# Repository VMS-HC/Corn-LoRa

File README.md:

A not so basic electronic project... This is a LoRa Board which is great for meshtastic but not great for my sanity when routing! This has a SX1262 radio chip and uses a RP2040 for the microcontroller along with a crystal oscillator for the RP2040 like any normal dev board. Corn LoRa also includes a *0900FM15D0039* as a IPD (integrated passive device) by Johanson which controls the balun and filtering (868-915MHz, may be different footprint) To switch between TX and RX, it uses an RF switch, controlled by DIO2; along with a PE4259 for a 2 channel switcher (as mentioned above!). It also uses a bulky non-standard Conn for an antenna! 
Ty for looking and have a good day! <3!
# Corn-LoRa PCB photo!
 3D Render photo!
 Schematic!

## FAQ

#### CAD? 
 Here! https://cad.onshape.com/documents/798bf0a7dc11aab5a7bf582d/w/40104e5f41c3cdcce0e1b7a0/e/90af93f35366755db2896de5?renderMode=0&uiState=6ae0c972e6e866bde4647e71
 
#### BOM?

There are 2 BOM technically one has the LCSC part numbers and the others is a quote from LCSC with links to parts too!

#### Is this good for beginners?

Yes and no, if you know EDA/Kicad basics and could make a dev board without trouble you should be able to make this!

#### How many layers is the PCB?

This is a 4 layer PCB with a Earth layer and a +3V3 layer!

#### Can I contribute?

YES YOU CAN!!!! Take a peek at the Contributing section for a better guide on contributing!

## Authors

- [@bobert3d](https://www.github.com/Bobert3D)

- [@vms-hc](https://www.github.com/VMS-HC)

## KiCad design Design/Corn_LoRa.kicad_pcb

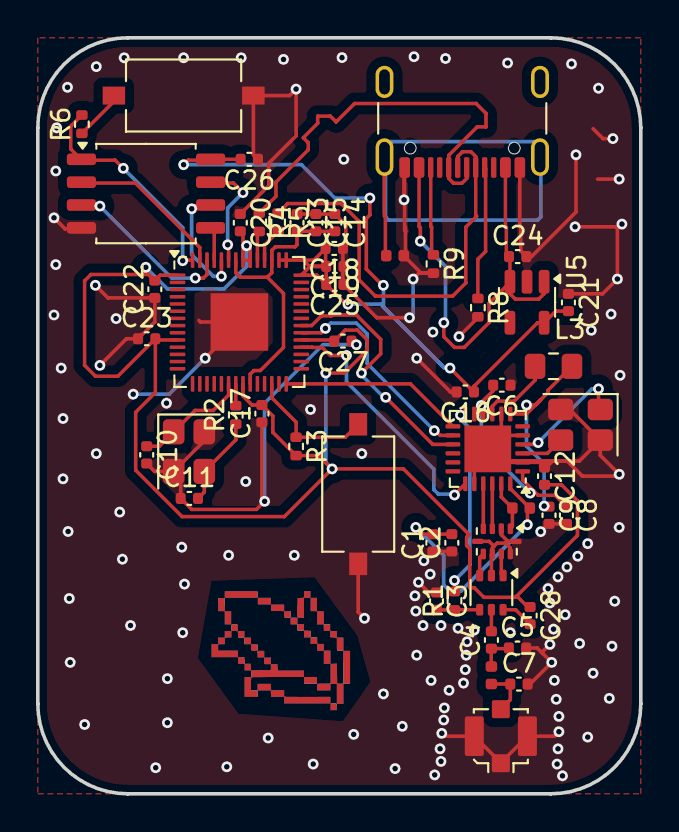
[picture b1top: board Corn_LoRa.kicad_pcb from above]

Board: 4 copper layers, 33.5 x 42.0 mm, 52 parts (0 on the bottom side), 43 nets.

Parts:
C1, C2: 47nF; C_0402_1005Metric
C3: 1nF; C_0402_1005Metric
C4: 39pF; C_0402_1005Metric
C5, C7, C12: 3.3pF; C_0402_1005Metric
C6, C8, C13, C14, C17, C18, C19, C20, C21, C22, C23, C26, C27: 100nF; C_0402_1005Metric
C9: 470nF; C_0402_1005Metric
C10, C11: 15pF; C_0402_1005Metric
C15, C16: 1uF; C_0402_1005Metric
C24, C25: 10uF; C_0402_1005Metric
C28: 10nF; C_0402_1005Metric
FB1: BLM15AX102SN1D; L_0402_1005Metric
FL1: 0900FM15K0039; Balun_Johanson_0900FM15K0039
J1: USB_C_Receptacle_USB2.0_16P; USB_C_Receptacle_GCT_USB4105-xx-A_16P_TopMnt_Horizontal
J2: Conn_Coaxial_Small; U.FL_Molex_MCRF_73412-0110_Vertical
L1, L2: 9.1nH; L_0402_1005Metric
L3: 15uH; L_0805_2012Metric_Pad1.15x1.40mm_HandSolder
R1: 100; R_0402_1005Metric
R2, R6: 1K; R_0402_1005Metric
R3: 10K; R_0402_1005Metric
R4, R5: 27.4; R_0402_1005Metric
R8, R9: 5.1K; R_0402_1005Metric
SW1: BOOTSEL; SW_Tactile_SPST_NO_Straight_CK_PTS636Sx25SMTRLFS
SW2: RESET; SW_Tactile_SPST_NO_Straight_CK_PTS636Sx25SMTRLFS
U1: PE4259; SOT-363_SC-70-6
U2: SX1262IMLTRT; QFN-24-1EP_4x4mm_P0.5mm_EP2.6x2.6mm
U3: W25Q128JVS; SOIC-8_5.3x5.3mm_P1.27mm
U4: RP2040; QFN-56-1EP_7x7mm_P0.4mm_EP3.2x3.2mm
U5: AP2112K-3.3; SOT-23-5
Y1: 32MHz; Crystal_SMD_3225-4Pin_3.2x2.5mm
Y2: 12MHz; Crystal_SMD_Abracon_ABM8G-4Pin_3.2x2.5mm

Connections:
+1V1: C13.2, C14.2, C15.2, U4.23 (DVDD), U4.45 (VREG_VOUT), U4.50 (DVDD)
+3V3: C12.2, C16.1, C17.2, C18.2, C19.2, C20.2, C21.2, C22.2, C23.2, C25.2, C26.2, C27.2, C28.1, R3.2, U3.8 (VCC), U4.1 (IOVDD), U4.10 (IOVDD), U4.22 (IOVDD), U4.33 (IOVDD), U4.42 (IOVDD), U4.43 (ADC_AVDD), U4.44 (VREG_IN), U4.48 (USB_VDD), U4.49 (IOVDD), U5.5 (VOUT)
/QSPI_SCLK: U3.6 (CLK), U4.52 (QSPI_SCLK)
/QSPI_SD0: U3.5 (DI/IO_{0}), U4.53 (QSPI_SD0)
/QSPI_SD1: U3.2 (DO/IO_{1}), U4.55 (QSPI_SD1)
/QSPI_SD2: U3.3 (~WP/IO_{2}), U4.54 (QSPI_SD2)
/QSPI_SD3: U3.7 (~HOLD/~RESET/IO_{3}), U4.51 (QSPI_SD3)
/QSPI_SS: R6.2, U3.1 (~CS), U4.56 (QSPI_SS)
/RUN: R3.1, SW2.2, U4.26 (RUN)
/SX_BUSY: U2.14 (BUSY), U4.34 (GPIO22)
/SX_DIO1: U2.13 (DIO1), U4.28 (GPIO17)
/SX_DIO2: R1.2, U2.12 (DIO2)
/SX_NRST: U2.15 (~RESET), U4.35 (GPIO23)
/SX_NSS: U2.19 (NSS), U4.32 (GPIO21)
/SX_RFI_N: FL1.3 (RFI_N), U2.22 (RFI_N)
/SX_RFI_P: FL1.4 (RFI_P), U2.21 (RFI_P)
/SX_RFO: FL1.1 (RFO), L1.2, U2.23 (RFO)
/SX_VR_PA: C1.2, C2.2, L1.1, U2.24 (VR_PA)
/SX_XTA: U2.3 (XTA), Y1.3
/SX_XTB: U2.4 (XTB), Y1.1
/USB_DM: J1.A7 (D-), J1.B7 (D-), R5.1
/USB_DP: J1.A6 (D+), J1.B6 (D+), R4.1
/XIN: C10.1, U4.20 (XIN), Y2.1
/XOUT: R2.2, U4.21 (XOUT)
Earth: C1.1, C2.1, C3.1, C5.2, C6.1, C7.2, C8.2, C9.2, C10.2, C11.1, C12.1, C13.1, C14.1, C15.1, C16.2, C17.1, C18.1, C19.1, C20.1, C21.1, C22.1, C23.1, C24.2, C25.1, C26.1, C27.1, FB1.2, FL1.2 (GND), FL1.5 (GND), FL1.7 (GND), FL1.9 (GND), FL1.10 (GND), J1.A1 (GND), J1.A12 (GND), J1.B1 (GND), J1.B12 (GND), J2.2 (Ext), R8.2, R9.2, SW1.1, SW2.1, U1.2 (GND), U2.2 (GND), U2.5 (GND), U2.8 (GND), U2.20 (GND), U2.25 (GND), U3.4 (GND), U4.57 (GND), U5.2 (GND), Y1.2, Y1.4, Y2.2, Y2.4
unnamed: C4.1, C5.1, L2.1
unnamed: C11.2, R2.1, Y2.3
unnamed: FL1.6 (SW_RFI), U1.3 (RF2)
unnamed: FL1.8 (SW_RFO), U1.1 (RF1)
unnamed: J1.A5 (CC1), R8.1
unnamed: J1.B5 (CC2), R9.1
unnamed: FB1.1, J1.S1 (SHIELD)
unnamed: C7.1, J2.1 (In), L2.2
unnamed: R6.1, SW1.2
unnamed: C3.2, R1.1, U1.4 (CTRL)
unnamed: C4.2, U1.5 (RFIN)
unnamed: C28.2, U1.6 (VDD)
unnamed: L3.1, U2.9 (DCC_SW)
unnamed: C6.2, C8.1, U2.1 (VDD_IN), U2.10 (VBAT), U2.11 (VBAT_IO)
unnamed: C9.1, L3.2, U2.7 (VREG)
unnamed: R5.2, U4.46 (USB_DM)
unnamed: R4.2, U4.47 (USB_DP)
VBUS: C24.1, J1.A4 (VBUS), J1.A9 (VBUS), J1.B4 (VBUS), J1.B9 (VBUS), U5.1 (VIN), U5.3 (EN)

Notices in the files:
README.md:
MIT License
